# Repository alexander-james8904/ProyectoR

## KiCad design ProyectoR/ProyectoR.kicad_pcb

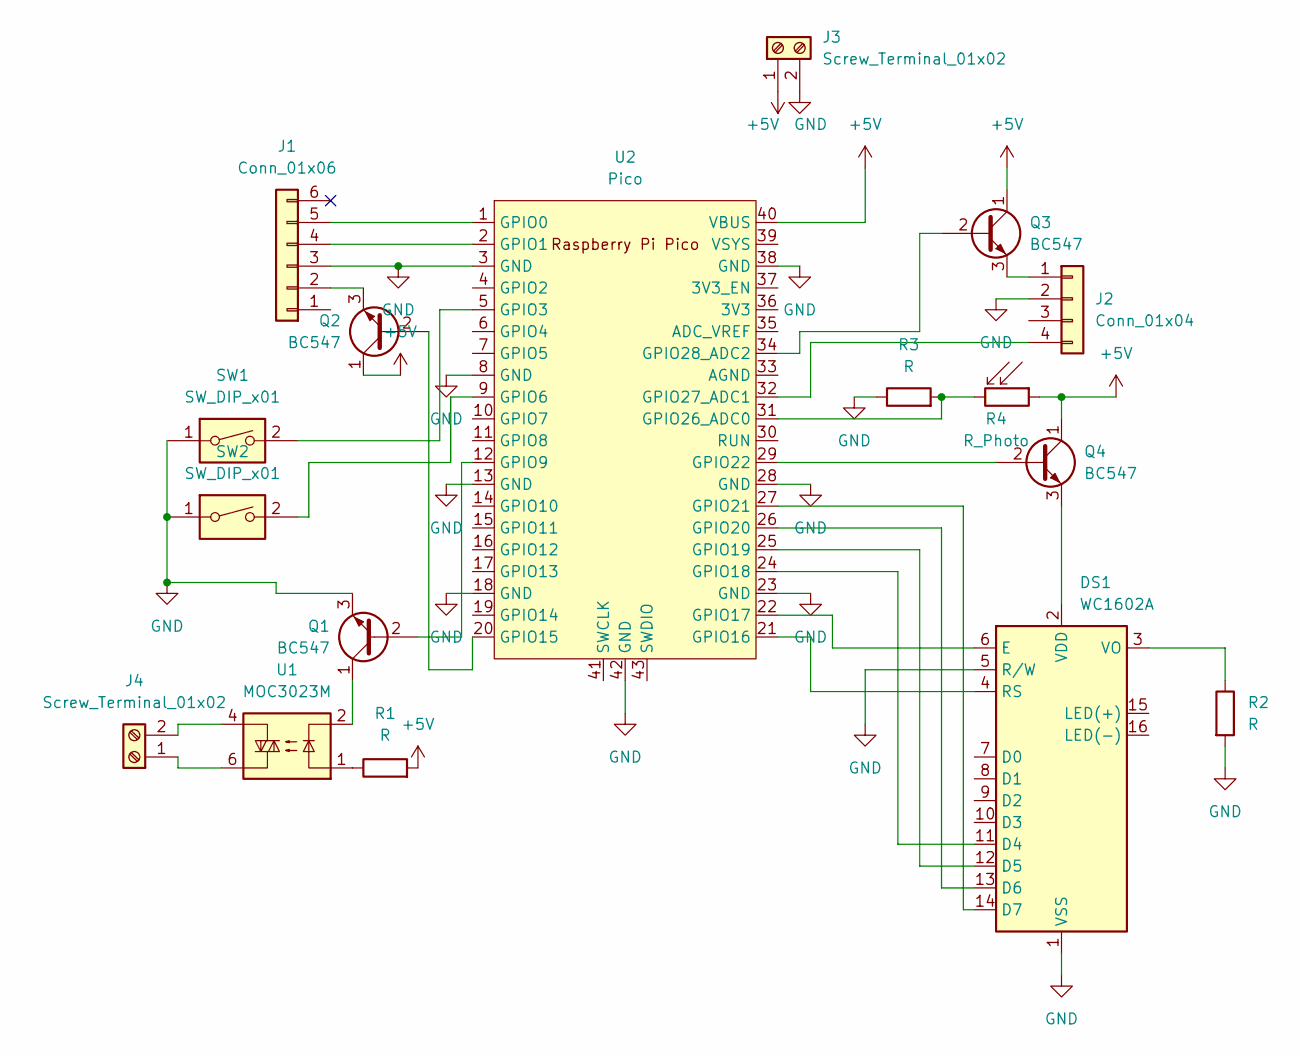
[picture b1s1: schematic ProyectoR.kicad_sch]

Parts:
DS1: WC1602A
J1: Conn_01x06; PinHeader_1x06_P2.54mm_Vertical
J2: Conn_01x04; PinHeader_1x04_P2.54mm_Vertical
J3: Screw_Terminal_01x02
J4: Screw_Terminal_01x02; TerminalBlock_Philmore_TB132_1x02_P5.00mm_Horizontal
Q1, Q2, Q3, Q4: BC547; TO-92_Inline
R1, R2, R3: R; R_Axial_DIN0207_L6.3mm_D2.5mm_P10.16mm_Horizontal
R4: R_Photo; PinHeader_1x02_P2.54mm_Vertical
SW1, SW2: SW_DIP_x01; SW_PUSH_6mm_H5mm
U1: MOC3023M; DIP-6_W7.62mm
U2: Pico; RPi_Pico_SMD_TH

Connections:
+5V: J3.1, Q2.1 (C), Q3.1 (C), Q4.1 (C), R1.2, R4.1, U2.40 (VBUS)
GND: DS1.1 (VSS), DS1.5 (R/W), J1.3, J2.2, J3.2, Q1.3 (E), R2.2, R3.1, SW1.1, SW2.1, U2.3 (GND), U2.8 (GND), U2.13 (GND), U2.18 (GND), U2.23 (GND), U2.28 (GND), U2.38 (GND), U2.42 (GND)
unnamed: DS1.2 (VDD), Q4.3 (E)
unnamed: DS1.3 (VO), R2.1
unnamed: DS1.4 (RS), U2.21 (GPIO16)
unnamed: DS1.6 (E), U2.22 (GPIO17)
unnamed: DS1.11 (D4), U2.24 (GPIO18)
unnamed: DS1.12 (D5), U2.25 (GPIO19)
unnamed: DS1.13 (D6), U2.26 (GPIO20)
unnamed: DS1.14 (D7), U2.27 (GPIO21)
unnamed: J1.2, Q2.3 (E)
unnamed: J1.4, U2.2 (GPIO1)
unnamed: J1.5, U2.1 (GPIO0)
unnamed: J2.1, Q3.3 (E)
unnamed: J2.4, U2.32 (GPIO27_ADC1)
unnamed: Q1.1 (C), U1.2
unnamed: Q2.2 (B), U2.20 (GPIO15)
unnamed: Q3.2 (B), U2.34 (GPIO28_ADC2)
unnamed: Q4.2 (B), U2.29 (GPIO22)
unnamed: R1.1, U1.1
unnamed: R3.2, R4.2, U2.31 (GPIO26_ADC0)
unnamed: SW1.2, U2.5 (GPIO3)
unnamed: SW2.2, U2.9 (GPIO6)
unnamed: J4.2, U1.4
unnamed: J4.1, U1.6
unnamed: Q1.2 (B), U2.12 (GPIO9)

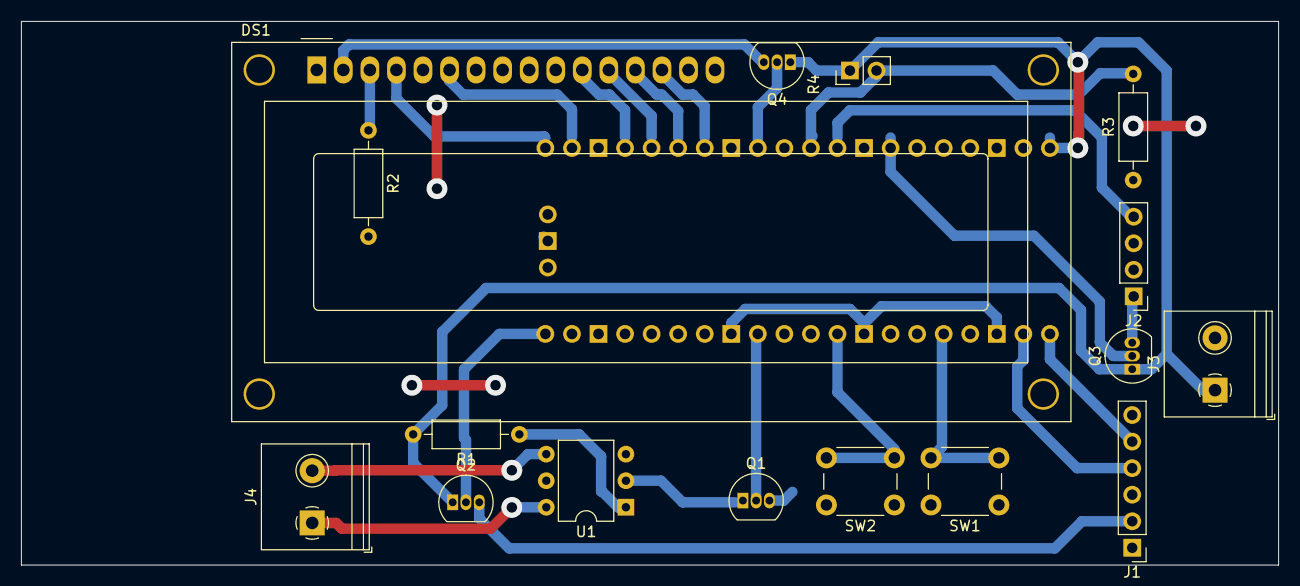
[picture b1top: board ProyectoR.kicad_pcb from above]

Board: 2 copper layers, 120.2 x 52.0 mm, 17 parts (1 on the bottom side), 26 nets.

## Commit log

2023-02-13 Add files via upload
    pcb 2
2023-02-13 Falta terminar
    Acomodé la librería de footprints, cambié tierras con GND, cambié fotoresistor por pin de 2.54mm entre otro
2023-02-14 V1.0.0
    Terminé el pcb, quedó con tres puentes nomás
2023-02-16 Aumento Clearance Power plane GND
    Aumenté la distancia mínima entre el power plane de GND así será más fácil a la hora de fabricarlo
